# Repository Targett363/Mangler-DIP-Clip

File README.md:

# Mangler-DIP-Clip
This is a KiCad reworking of @unexpectedmaker SAMD21G-Mangler https://github.com/UnexpectedMaker/SAMD21G-Mangler or https://www.tindie.com/products/seonr/samd21g-mangler/ to add support for a clip style 48pin TQFP to 48pin DIP converter module.

This works for burning the bootloader with an Atmel ICE and programming through the USB however you will notice that I've also broken out pins to use this as a proto board.

I have tested the board for bootloader and usb operation and these work, I had to rework the broken out pins and label them the new version is correct now but untested. I have laveled the pins as in the Arduino M0 board library.

Included files are the KiCad project files and the gerbers needed to make this board.

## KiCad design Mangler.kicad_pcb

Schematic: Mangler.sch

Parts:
C1, C2: 10uF; C_1206_3216Metric
C3: 0.1uF; C_0805_2012Metric
C4, C5, C8: 1uF; C_0603_1608Metric
C6, C7: 12.5pF; C_0603_1608Metric
D1: SWDIO; LED_0201_0603Metric
D2: SWCLK; LED_0201_0603Metric
J1: USB; USB_Micro-B_Molex_47346-0001
J2: ICE 10pin; PinSocket_2x05_P1.27mm_Vertical_SMD
J3: ANALOG; PinSocket_1x06_P2.54mm_Vertical
J4: PWR/RESET; PinSocket_1x05_P2.54mm_Vertical
J5: DIGITAL; PinSocket_1x14_P2.54mm_Vertical
J6: I2C; PinSocket_1x04_P2.54mm_Vertical
J7: SPI; PinSocket_1x05_P2.54mm_Vertical
R1, R2: 2.2K; R_0603_1608Metric
U1: TLV1963-33DGYR; SOT-223-3_TabPin2
U2: SAMD21G18A-AF; DIP-48_W16.4mm_Socket
Y1: Crystal; Crystal_SMD_G8-2Pin_3.2x1.5mm

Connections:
+3V3: C2.1, C3.1, C4.1, C5.1, J2.1, J4.1, J4.2, J6.1, J7.1, U1.3 (VO), U2.6, U2.17, U2.36, U2.44
+5V: C1.1, J1.1, U1.1 (VI)
A0: J3.1, U2.3
A1: J3.2, U2.7
A2: J3.3, U2.8
A3: J3.4, U2.9
A4: J3.5, U2.10
A5: J3.6, U2.47
D0: J5.1, U2.16
D1: J5.2, U2.15
D5: J5.6, U2.24
D6: J5.7, U2.29
D9: J5.10, U2.12
D10: J5.11, U2.27
D11: J5.12, U2.25
D12: J5.13, U2.28
D13: J5.14, U2.26
D+: J1.3, U2.34
D-: J1.2, U2.33
GND: C1.2, C2.2, C3.2, C5.2, C6.2, C7.2, C8.2, D1.1, D2.1, J1.5, J1.6, J2.3, J2.5, J4.4, J4.5, J5.3, J5.4, J5.5, J5.8, J5.9, J6.4, J7.5, U1.2 (GND), U2.5, U2.18, U2.35, U2.42
MISO: J7.4, U2.21
MOSI: J7.3, U2.19
unnamed: C4.2, U2.43
unnamed: C6.1, U2.1, Y1.1
unnamed: C7.1, U2.2, Y1.2
unnamed: C8.1, U2.4
unnamed: D1.2, R1.2
unnamed: D2.2, R2.2
RESET: J2.10, J4.3, U2.40
SCK: J7.2, U2.20
SCL: J6.2, U2.32
SDA: J6.3, U2.31
SWCLK: J2.4, R2.1, U2.45
SWDIO: J2.2, R1.1, U2.46

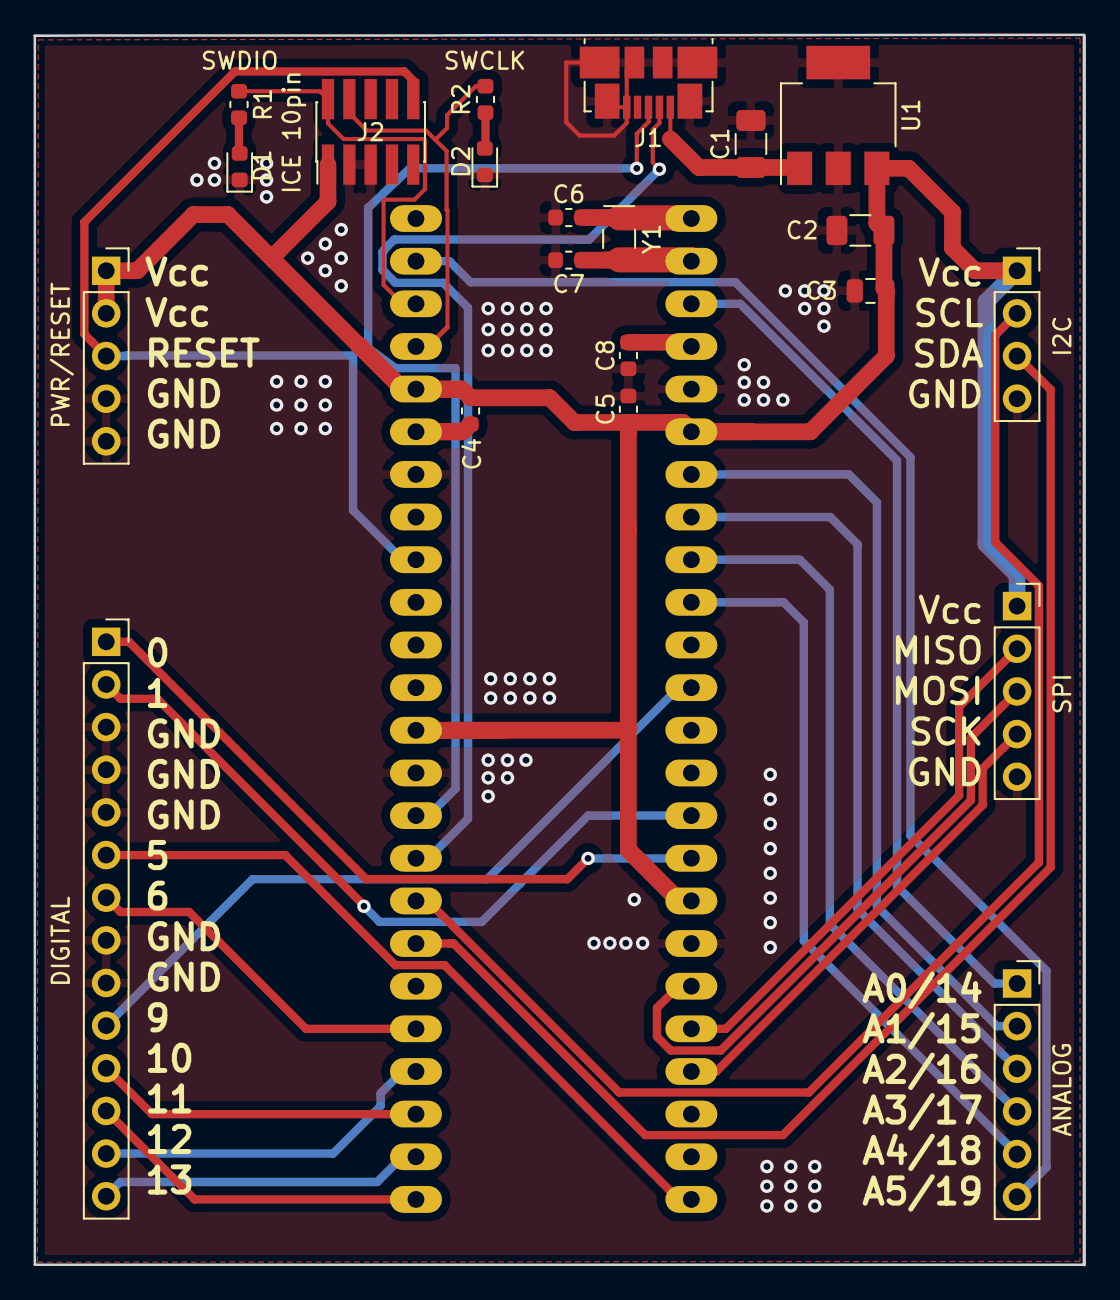
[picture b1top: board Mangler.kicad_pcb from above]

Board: 2 copper layers, 62.5 x 73.2 mm, 22 parts (1 on the bottom side), 34 nets.

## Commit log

2019-01-16 This is a KiCad reworking of @unexpectedmaker SAMD21G-Mangler
    https://github.com/UnexpectedMaker/SAMD21G-Mangler or
    https://www.tindie.com/products/seonr/samd21g-mangler/ to add support
    for a clip style chip holder on a 48pin DIP converter module.
2019-01-17 Pin updates
    Pin location updates and pin labals on silkscreen
2019-01-17 Updated Pins and Gerbers
